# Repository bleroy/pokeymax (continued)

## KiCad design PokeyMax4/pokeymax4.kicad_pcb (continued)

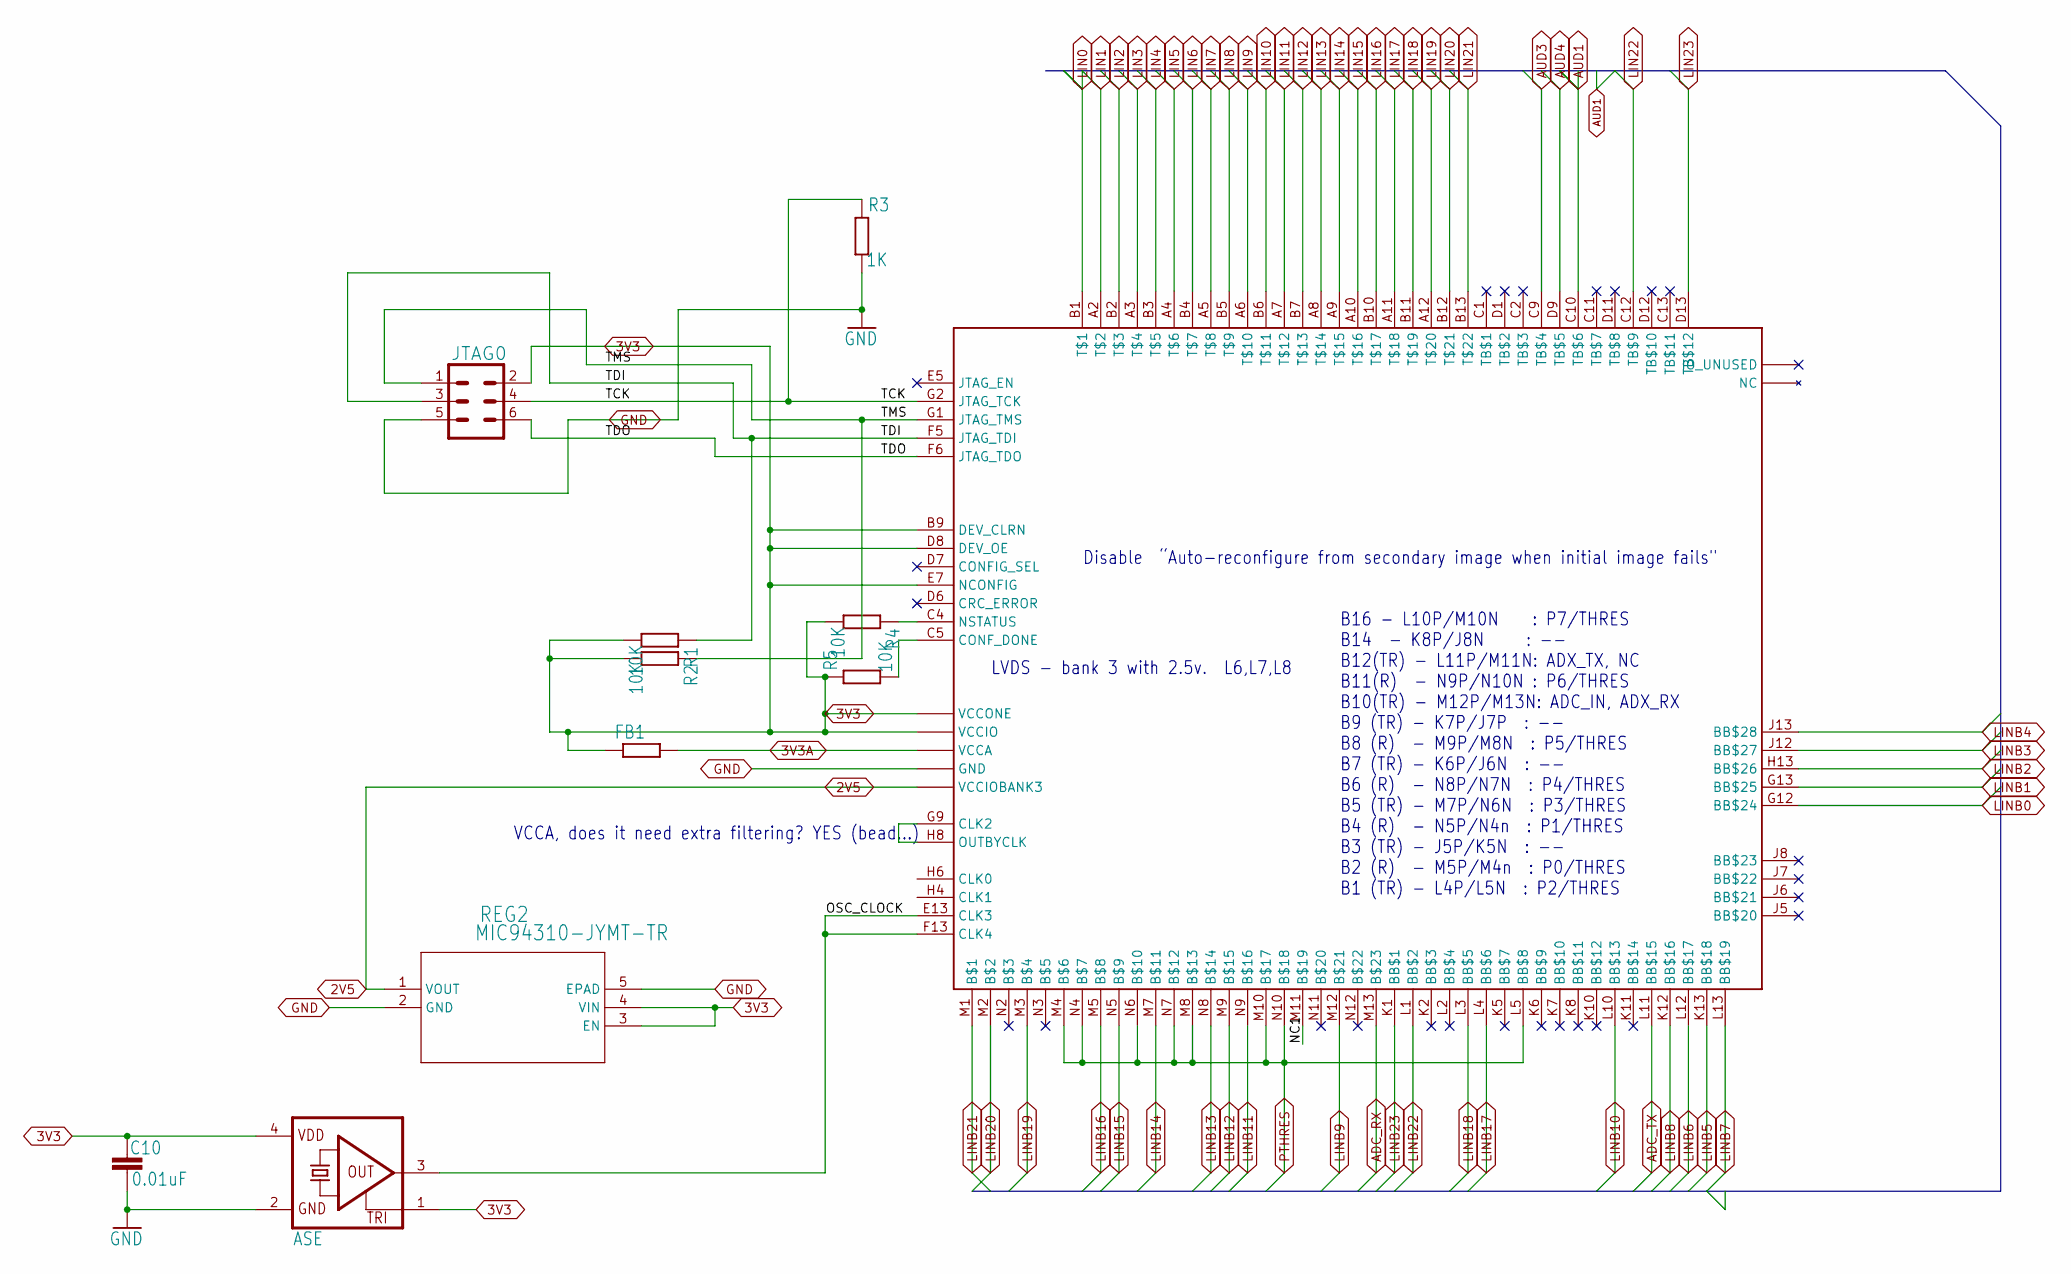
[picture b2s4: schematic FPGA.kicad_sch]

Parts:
C10: 0.01uF; C0402; LCSC Part # C43253
FB1: R-EU_R0402; R0402; LCSC Part # C710330
JTAG0: CONN_03X2LOCK; 2X3_LOCK
R1, R2, R4, R5: 10K; R0402; LCSC Part # C103199
R3: 1K; R0402; LCSC Part # C107079
REG2: MIC94310-JYMT-TR; TDFN4_1P2X1P6_MCH; LCSC Part # C622559
U3: MAX10; U169SMALL; LCSC Part # C1521935
X1: ASE; LCSC Part # C7431354

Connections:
2V5: REG2.1 (VOUT), U3.L6 (VCCIOBANK3), U3.L7 (VCCIOBANK3), U3.L8 (VCCIOBANK3); also elsewhere on the board
3V3: C10.1, FB1.1, JTAG0.2, R1.2, R2.2, R4.2, R5.1, REG2.3 (EN), REG2.4 (VIN), U3.B9 (DEV_CLRN), U3.C6 (VCCIO), U3.C7 (VCCIO), U3.C8 (VCCIO), U3.D8 (DEV_OE), U3.E7 (NCONFIG), U3.F2 (VCCIO), U3.F7 (VCCONE), U3.F11 (VCCIO), U3.G3 (VCCIO), U3.G6 (VCCONE), U3.G8 (VCCONE), U3.G11 (VCCIO), U3.H7 (VCCONE), U3.H11 (VCCIO), U3.J3 (VCCIO), U3.J11 (VCCIO), U3.K3 (VCCIO), X1.1 (TRI), X1.4 (VDD); also elsewhere on the board
3V3A: FB1.2, U3.D4 (VCCA), U3.D10 (VCCA), U3.K4 (VCCA), U3.K9 (VCCA); also elsewhere on the board
/FPGA/NC1: U3.M11
/FPGA/OSC_CLOCK: U3.E13 (CLK3), U3.F13 (CLK4), X1.3 (OUT)
/FPGA/TCK: JTAG0.4, R3.1, U3.G2 (JTAG_TCK)
/FPGA/TDI: JTAG0.3, R1.1, U3.F5 (JTAG_TDI)
/FPGA/TDO: JTAG0.6, U3.F6 (JTAG_TDO)
/FPGA/TMS: JTAG0.1, R2.1, U3.G1 (JTAG_TMS)
ADC_RX: U3.M13; also elsewhere on the board
ADC_TX: U3.L11 (BB$15); also elsewhere on the board
AUD1: U3.C10 (TB$6); also elsewhere on the board
AUD3: U3.C9 (TB$4); also elsewhere on the board
AUD4: U3.D9 (TB$5); also elsewhere on the board
GND: C10.2, JTAG0.5, R3.2, REG2.2 (GND), REG2.5 (EPAD), U3.A1 (GND), U3.A13 (GND), U3.B8 (GND), U3.C3 (GND), U3.D5 (GND), U3.E11 (GND), U3.F3 (GND), U3.G7 (GND), U3.H12 (GND), U3.J4 (GND), U3.L9 (GND), U3.M6 (GND), U3.N1 (GND), U3.N13 (GND), X1.2 (GND); also elsewhere on the board
LIN0: U3.B1; also elsewhere on the board
LIN1: U3.A2; also elsewhere on the board
LIN2: U3.B2; also elsewhere on the board
LIN3: U3.A3; also elsewhere on the board
LIN4: U3.B3; also elsewhere on the board
LIN5: U3.A4; also elsewhere on the board
LIN6: U3.B4; also elsewhere on the board
LIN7: U3.A5; also elsewhere on the board
LIN8: U3.B5; also elsewhere on the board
LIN9: U3.A6; also elsewhere on the board
LIN10: U3.B6; also elsewhere on the board
LIN11: U3.A7; also elsewhere on the board
LIN12: U3.B7; also elsewhere on the board
LIN13: U3.A8; also elsewhere on the board
LIN14: U3.A9; also elsewhere on the board
LIN15: U3.A10; also elsewhere on the board
LIN16: U3.B10; also elsewhere on the board
LIN17: U3.A11; also elsewhere on the board
LIN18: U3.B11; also elsewhere on the board
LIN19: U3.A12; also elsewhere on the board
LIN20: U3.B12; also elsewhere on the board
LIN21: U3.B13; also elsewhere on the board
LIN22: U3.C12 (TB$9); also elsewhere on the board
LIN23: U3.D13 (TB$12); also elsewhere on the board
LINB0: U3.G12 (BB$24); also elsewhere on the board
LINB1: U3.G13 (BB$25); also elsewhere on the board
LINB2: U3.H13 (BB$26); also elsewhere on the board
LINB3: U3.J12 (BB$27); also elsewhere on the board
LINB4: U3.J13 (BB$28); also elsewhere on the board
LINB5: U3.K13 (BB$18); also elsewhere on the board
LINB6: U3.L12 (BB$17); also elsewhere on the board
LINB7: U3.L13 (BB$19); also elsewhere on the board
LINB8: U3.K12 (BB$16); also elsewhere on the board
LINB9: U3.M12; also elsewhere on the board
LINB10: U3.L10 (BB$13); also elsewhere on the board
LINB11: U3.N9; also elsewhere on the board
LINB12: U3.M9; also elsewhere on the board
LINB13: U3.N8; also elsewhere on the board
LINB14: U3.M7; also elsewhere on the board
LINB15: U3.N5; also elsewhere on the board
LINB16: U3.M5; also elsewhere on the board
LINB17: U3.L4 (BB$6); also elsewhere on the board
LINB18: U3.L3 (BB$5); also elsewhere on the board
LINB19: U3.M3; also elsewhere on the board
LINB20: U3.M2; also elsewhere on the board
LINB21: U3.M1; also elsewhere on the board
LINB22: U3.L1 (BB$2); also elsewhere on the board
LINB23: U3.K1 (BB$1); also elsewhere on the board
unnamed: U3.G9 (CLK2), U3.H8 (OUTBYCLK)
unnamed: R5.2, U3.C5 (CONF_DONE)
unnamed: R4.1, U3.C4 (NSTATUS)
PTHRES: U3.L5 (BB$8), U3.M4, U3.M8, U3.M10, U3.N4, U3.N6, U3.N7, U3.N10; also elsewhere on the board

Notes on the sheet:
Disable “Auto-reconfigure from secondary image when initial image fails"
B16 - L10P/M10N : P7/THRES B14 - K8P/J8N : -- B12(TR) - L11P/M11N: ADX_TX, NC B11(R) - N9P/N10N : P6/THRES B10(TR) - M12P/M13N: ADC_IN, ADX_RX B9 (TR) - K7P/J7P : -- B8 (R) - M9P/M8N : P5/THRES B7 (TR) - K6P/J6N : -- B6 (R) - N8P/N7N : P4/THRES B5 (TR) - M7P/N6N : P3/THRES B4 (R) - N5P/N4n : P1/THR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
LVDS - bank 3 with 2.5v. L6,L7,L8
VCCA, does it need extra filtering? YES (bead...)

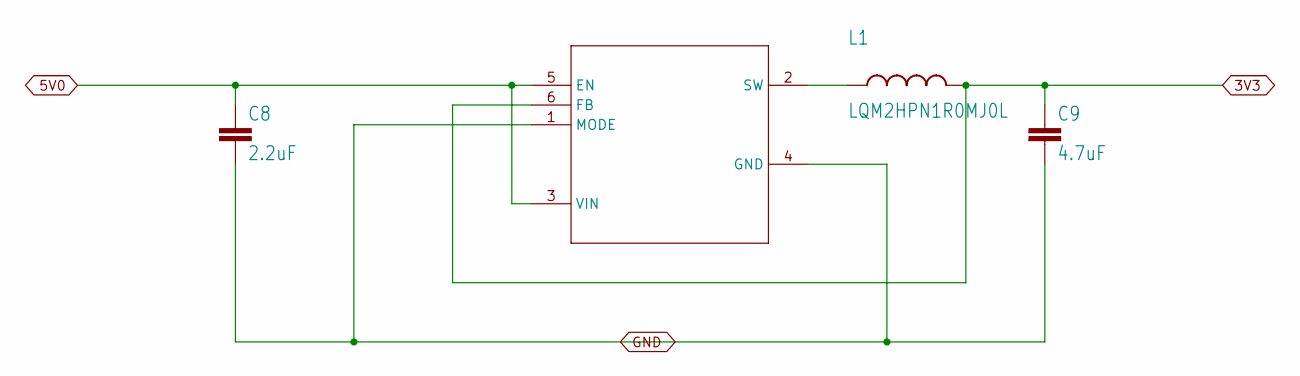
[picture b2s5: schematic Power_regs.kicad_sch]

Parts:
C8: 2.2uF; C0402; LCSC Part # C43922
C9: 4.7uF; C0402; LCSC Part # C112433
L1: LQM2HPN1R0MJ0L; INDC1008X04; LCSC Part # C216157
REG1: TPS62237DRYR; DRY6; LCSC Part # C398923

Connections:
3V3: C9.1, L1.2, REG1.6 (FB); also elsewhere on the board
5V0: C8.1, REG1.3 (VIN), REG1.5 (EN); also elsewhere on the board
GND: C8.2, C9.2, REG1.1 (MODE), REG1.4 (GND); also elsewhere on the board
unnamed: L1.1, REG1.2 (SW)

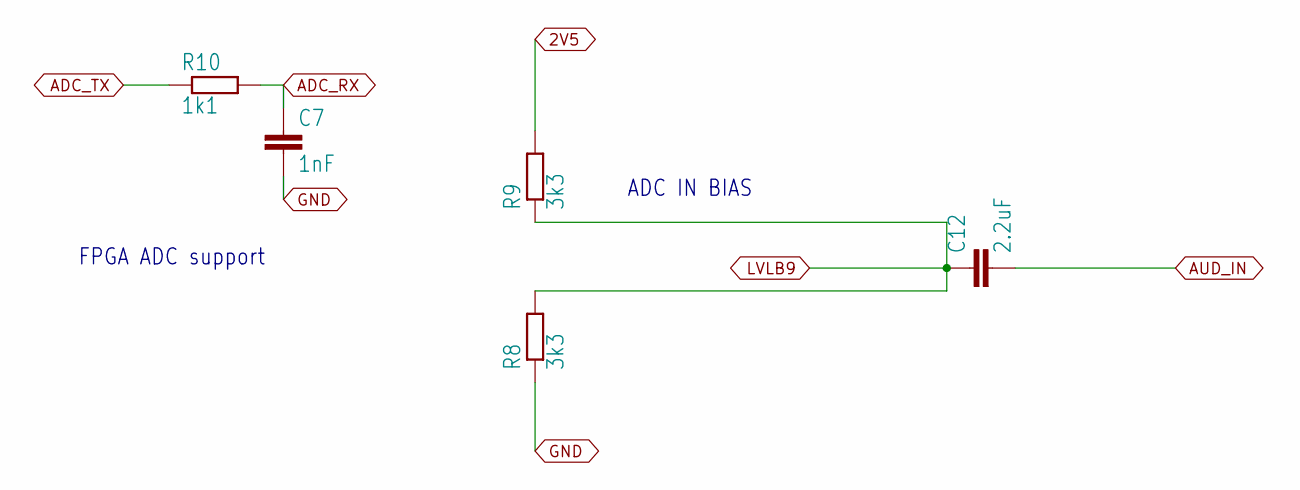
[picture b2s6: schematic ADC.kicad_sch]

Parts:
C7: 1nF; C0402; LCSC Part # C1636
C12: 2.2uF; C0402; LCSC Part # C43922
R8, R9: 3k3; R0402; LCSC Part # C72816
R10: 1k1; R0402; LCSC Part # C140120

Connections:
2V5: R9.2; also elsewhere on the board
ADC_RX: C7.1, R10.2; also elsewhere on the board
ADC_TX: R10.1; also elsewhere on the board
AUD_IN: C12.2; also elsewhere on the board
GND: C7.2, R8.1; also elsewhere on the board
LVLB9: C12.1, R8.2, R9.1; also elsewhere on the board

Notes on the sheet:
ADC IN BIAS
FPGA ADC support

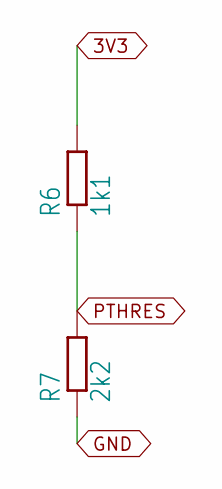
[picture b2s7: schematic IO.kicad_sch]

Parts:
R6: 1k1; R0402; LCSC Part # C140120
R7: 2k2; R0402; LCSC Part # C294652

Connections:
3V3: R6.2; also elsewhere on the board
GND: R7.1; also elsewhere on the board
PTHRES: R6.1, R7.2; also elsewhere on the board

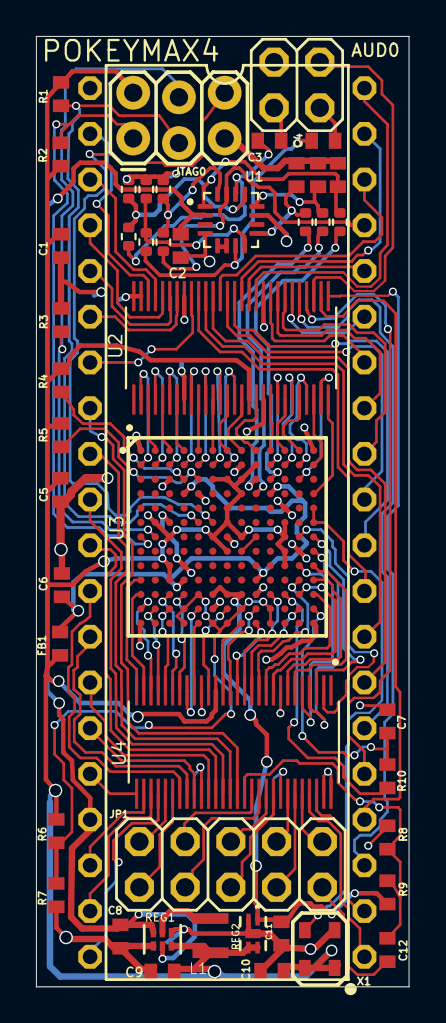
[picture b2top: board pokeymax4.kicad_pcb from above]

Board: 2 copper layers, 20.7 x 52.8 mm, 47 parts (0 on the bottom side), 129 nets.

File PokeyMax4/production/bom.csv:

Designator,Footprint,Quantity,Value,LCSC Part #
"C1, C11, C2, C5, C6",C0402,5,0.1uF,C88219
C10,C0402,1,0.01uF,C43253
"C12, C3, C4, C8",C0402,4,2.2uF,C43922
"C13, C14, C15",C0402,3,18nF,C107079
C7,C0402,1,1nF,C1636
C9,C0402,1,4.7uF,C112433
FB1,R0402,1,R-EU_R0402,C710330
L1,INDC1008X04,1,LQM2HPN1R0MJ0L,C216157
"R1, R2, R4, R5",R0402,4,10K,C103199
"R10, R6",R0402,2,1k1,C140120
"R11, R12, R13",0402,3,560R,
"R14, R15, R16",0402,3,10k,
"R17, R18, R19",0402,3,20k,
R3,R0402,1,1K,C107079
R7,R0402,1,2k2,C294652
"R8, R9",R0402,2,3k3,C72816
REG1,DRY6,1,TPS62237DRYR,C398923
REG2,TDFN4_1P2X1P6_MCH,1,MIC94310-JYMT-TR,C622559
U1,QFN50P300X300X100-16N,1,TSV854IQ4T,C2058240
"U2, U4",56TVSOP_SMALL,2,SN74CB3T16211SM,C2674751
U3,U169SMALL,1,MAX10,C1521935
X1,ASE,1,ASE,C7431354

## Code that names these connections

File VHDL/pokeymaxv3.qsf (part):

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set_global_assignment -name DEVICE_FILTER_PIN_COUNT 169
set_global_assignment -name DEVICE_FILTER_SPEED_GRADE 8
set_global_assignment -name ERROR_CHECK_FREQUENCY_DIVISOR 256
set_location_assignment PIN_B3 -to PHI2   #B3,LVLA4,PHI
set_location_assignment PIN_A3 -to D[7]   #A3,LVLA3,D7
set_location_assignment PIN_B2 -to D[6]   #B2,LVLA2,D6
set_location_assignment PIN_A2 -to D[5]   #A2,LVLA1,LVL5,D5
set_location_assignment PIN_B1 -to D[4]   #B1,LVLA0,D4
set_location_assignment PIN_A4 -to D[3]   #A4,LVLA5,D3
set_location_assignment PIN_A11 -to D[2]  #A11,LVLA17,D2
set_location_assignment PIN_B10 -to D[1]  #B10,LVLA16,D1
set_location_assignment PIN_A10 -to D[0]  #A10,LVLA15,D0
set_location_assignment PIN_A5 -to CS0_N  #A5,LVLA,CS0_N
set_location_assignment PIN_B6 -to CS1    #B6,LVLA10,CS1
set_location_assignment PIN_B4 -to IRQ    #B4,LVLA6,IRQ_N
set_location_assignment PIN_B5 -to W_N    #B5,LVLA8,RW
set_location_assignment PIN_A7 -to SID    #A7,LVLA11,SID
set_location_assignment PIN_A9 -to SOD    #A9,LVLA14,SOD
set_location_assignment PIN_A8 -to ACLK   #A8,LVLA13,ACLK
set_location_assignment PIN_B7 -to BCLK   #B7,LVLA12,BCLK
set_location_assignment PIN_B11 -to A[0]  #B11,LVLA18,A0
set_location_assignment PIN_B12 -to A[1]  #B12,LVLA20,A1
set_location_assignment PIN_C13 -to A[2]   #C13,LVLA22,A2
set_location_assignment PIN_A6 -to A[3]   #A6,LVLA9,A3

set_location_assignment PIN_N2 -to PADDLE[5]  #11=N2 POT7 p5
set_location_assignment PIN_N3 -to PADDLE[1]  #15=N3 POT6 p1
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set_location_assignment PIN_N9 -to PADDLE[2]  #12=N9 POT0 p2
set_location_assignment PIN_M2 -to POTRESET_N  #POTRESET - M2

set_location_assignment PIN_C11 -to AUD[1] #AUD1 - C11
set_location_assignment PIN_D11 -to AUD[3] #AUD3 - D11
set_location_assignment PIN_C12 -to AUD[2] #AUD2 - C12
set_location_assignment PIN_D12 -to AUD[4] #AUD4 - D12

set_location_assignment PIN_M3 -to IOX_RST   #IOX_RST - M3
set_location_assignment PIN_M4 -to IOX_SDA   #IOX_SDA - M4
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set_location_assignment PIN_H6 -to CLK0      #CLK0 - H6
set_location_assignment PIN_H4 -to CLK1      #CLK1 - H4

set_location_assignment PIN_A12 -to EXT[1] #A12,LVLA19,EXT3
set_location_assignment PIN_B13 -to EXT[2] #B13,LVLA21,EXT2
set_location_assignment PIN_D13 -to EXT[3] #D13,LVLA23,EXT1
set_location_assignment PIN_M9 -to EXT[4] #LVLB0  EXT4  - M9
set_location_assignment PIN_M10 -to EXT[5] #LVLB1  EXT5  - M10
set_location_assignment PIN_N10 -to EXT[6] #LVLB2  EXT6  - N10
set_location_assignment PIN_M11 -to EXT[7] #LVLB3  EXT7  - M11
set_location_assignment PIN_N11 -to EXT[8] #LVLB4  EXT8  - N11
set_location_assignment PIN_M12 -to EXT[9] #LVLB5  EXT9  - M12
set_location_assignment PIN_N12 -to EXT[10] #LVLB6  EXT10 - N12
set_location_assignment PIN_M13 -to EXT[11] #LVLB7  EXT11 - M13

set_instance_assignment -name WEAK_PULL_UP_RESISTOR ON -to IOX_RST
set_instance_assignment -name WEAK_PULL_UP_RESISTOR ON -to IOX_INT
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
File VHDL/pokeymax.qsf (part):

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set_global_assignment -name DEVICE_FILTER_PIN_COUNT 169
set_global_assignment -name DEVICE_FILTER_SPEED_GRADE 8
set_global_assignment -name ERROR_CHECK_FREQUENCY_DIVISOR 256
set_location_assignment PIN_B1 -to PHI2    #B1,LIN0,LVL8,PHI
set_location_assignment PIN_A2 -to D[7]   #A2,LIN1,LVL7,D7
set_location_assignment PIN_B2 -to D[6]   #B2,LIN2,LVL6,D6
set_location_assignment PIN_A3 -to D[5]   #A3,LIN3,LVL5,D5
set_location_assignment PIN_B3 -to D[4]   #B3,LIN4,LVL4,D4
set_location_assignment PIN_A4 -to D[3]   #A4,LIN5,LVL3,D3
set_location_assignment PIN_B4 -to CS0_N  #B4,LIN6,LVL21,CS0_N
set_location_assignment PIN_A5 -to CS1    #A5,LIN7,LVL9,CS1
set_location_assignment PIN_B5 -to IRQ    #B5,LIN8,LVL14,IRQ_N
set_location_assignment PIN_A6 -to W_N    #A6,LIN9,LVL15,RW
set_location_assignment PIN_B6 -to SOD    #B6,LIN10,LVL13,SOD
set_location_assignment PIN_A7 -to ACLK   #A7,LIN11,LVL12,ACLK
set_location_assignment PIN_B7 -to BCLK   #B7,LIN12,LVL11,BCLK
set_location_assignment PIN_A8 -to A[3]   #A8,LIN13,LVL16,A3
set_location_assignment PIN_A9 -to SID    #A9,LIN14,LVL10,SID
set_location_assignment PIN_A10 -to D[2]  #A10,LIN15,LVL2,D2
set_location_assignment PIN_B10 -to D[1]  #B10,LIN16,LVL1,D1
set_location_assignment PIN_A11 -to D[0]  #A11,LIN17,LVL0,D0
set_location_assignment PIN_B11 -to A[0]  #B11,LIN18,LVL19,A0
set_location_assignment PIN_A12 -to EXT[1] #A12,LIN19,LVL23,EXT3
set_location_assignment PIN_B12 -to A[1]  #B12,LIN20,LVL18,A1
set_location_assignment PIN_B13 -to EXT[2] #B13,LIN21,LVL22,EXT2
set_location_assignment PIN_C11 -to AUD[1] #C11,AUD1,AUDF1,AUD
set_location_assignment PIN_D11 -to AUD[3] #D11,AUD2,AUDF4,AUDEXT2
set_location_assignment PIN_C12 -to AUD[4] #C12,AUD3,AUDF2,AUDEXT3
set_location_assignment PIN_D12 -to AUD[2] #D12,AUD4,AUDF3,AUDEXT1
set_location_assignment PIN_C13 -to A[2]   #C13,LIN22,LVL17,A2
set_location_assignment PIN_D13 -to EXT[3] #D13,LIN23,LVL20,EXT1
set_location_assignment PIN_N2 -to PADDLE[5]  #N2,PIN3,POT7,P5
set_location_assignment PIN_N3 -to PADDLE[1]  #N3,PIN2,POT6,P1
set_location_assignment PIN_N4 -to PADDLE[4]  #N4,PIN0,POT5,P4
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
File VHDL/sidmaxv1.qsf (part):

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set_global_assignment -name DEVICE_FILTER_SPEED_GRADE 8
set_global_assignment -name ERROR_CHECK_FREQUENCY_DIVISOR 256

set_location_assignment PIN_B1 -to PHI2 #B1,LIN0,P6,PHI
set_location_assignment PIN_A2 -to RST_N #A2,LIN1,P5,RST
set_location_assignment PIN_B2 -to CS_N #B2,LIN2,P8,CS_N
set_location_assignment PIN_A3 -to W_N #A3,LIN3,P7,RW_N
set_location_assignment PIN_B3 -to A[0] #B3,LIN4,P9,A0
set_location_assignment PIN_A4 -to A[1] #A4,LIN5,P10,A1
set_location_assignment PIN_B4 -to A[2] #B4,LIN6,P11,A2
set_location_assignment PIN_A5 -to A[3] #A5,LIN7,P12,A3
set_location_assignment PIN_B5 -to A[4] #B5,LIN8,P13,A4
set_location_assignment PIN_A6 -to D[0] #A6,LIN9,P15,D0
set_location_assignment PIN_B6 -to D[1] #B6,LIN10,P16,D1
set_location_assignment PIN_A7 -to D[2] #A7,LIN11,P17,D2
set_location_assignment PIN_B7 -to D[3] #B7,LIN12,P18,D3
set_location_assignment PIN_A8 -to D[4] #A8,LIN13,P19,D4
set_location_assignment PIN_A9 -to D[7] #A9,LIN14,P22,D7
set_location_assignment PIN_A10 -to D[6] #A10,LIN15,P21,D6
set_location_assignment PIN_B10 -to D[5] #B10,LIN16,P20,D5
set_location_assignment PIN_A11 -to EXT[3] #A11,LIN17,EXT1
set_location_assignment PIN_B11 -to EXT[2] #B11,LIN18,EXT2
set_location_assignment PIN_A12 -to EXT[1] #A12,LIN19,EXT3
set_location_assignment PIN_B12 -to EXT[4] #B12,LIN20,EXT4

set_location_assignment PIN_C9 -to AUDIO_LEFT ###C9,AUD3,AUDIO_LEFT
set_location_assignment PIN_D9 -to AUDIO_RIGHT ###D9,AUD4,AUDIO_RIGHT
set_location_assignment PIN_C10 -to AUDIO_INT ###C10,AUD1,AUDIO_INT

set_location_assignment PIN_L10 -to EXT_IN_p #L10,LIN22,P26,EXT_IN
set_location_assignment PIN_M10 -to EXT_IN_n #ADC_RX #M10,ADC_RX,
set_location_assignment PIN_K8 -to ADC_TX_p #K8,ADC_TX,
set_location_assignment PIN_J8 -to ADC_TX_n #K8,ADC_TX,

set_location_assignment PIN_K7 -to POTY_p #K7,LIN21,P23,POTY
set_location_assignment PIN_J7 -to POTY_n #K7,LIN21,P23,POTY
set_location_assignment PIN_K6 -to POTY_RESET #K6,POTY_RESET,
#set_location_assignment PIN_J6 -to POTY_RESET(n) ###J6,NC3,
set_location_assignment PIN_L11 -to POTX_p #L11,LIN23,P24,POTX
set_location_assignment PIN_M11 -to POTX_n #L11,LIN23,P24,POTX
set_location_assignment PIN_M12 -to POTX_RESET #M12,POTX_RESET,
#set_location_assignment PIN_M13 -to POTX_RESET(n) ###M13,NC2,

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
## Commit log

2024-04-17 Initial push of KiCad import of PokeyMax 4 files
2024-04-18 Add VHDL
2024-08-10 Update the v4 board
2024-08-18 Updates for JLCPCB fabrication and parts library
2024-08-21 Final adjustements to production files for JLC
2024-08-21 Nothing really
2024-08-22 Update BOM from 0402 to 0603 where relevant
2024-08-25 Pokeymax 4s WIP
2024-08-25 Complete routing of Pokeymax 4s
    Removed backup dirs from repo
2024-08-25 PokeyMax 4s silkscreen
2024-08-25 PokeyMax 4s fabrication files
2024-08-27 Add A4 to PokeyMax 4s
    Reroute accordingly
2024-08-28 Last adjustments to 4s
2024-08-28 Fix typo on 4s board
2025-06-21 Fix LIN22 to AUD1 erroneous connection
2025-06-21 Bump rev number to 1.1
2025-06-21 Rebuild prod files with rev number
